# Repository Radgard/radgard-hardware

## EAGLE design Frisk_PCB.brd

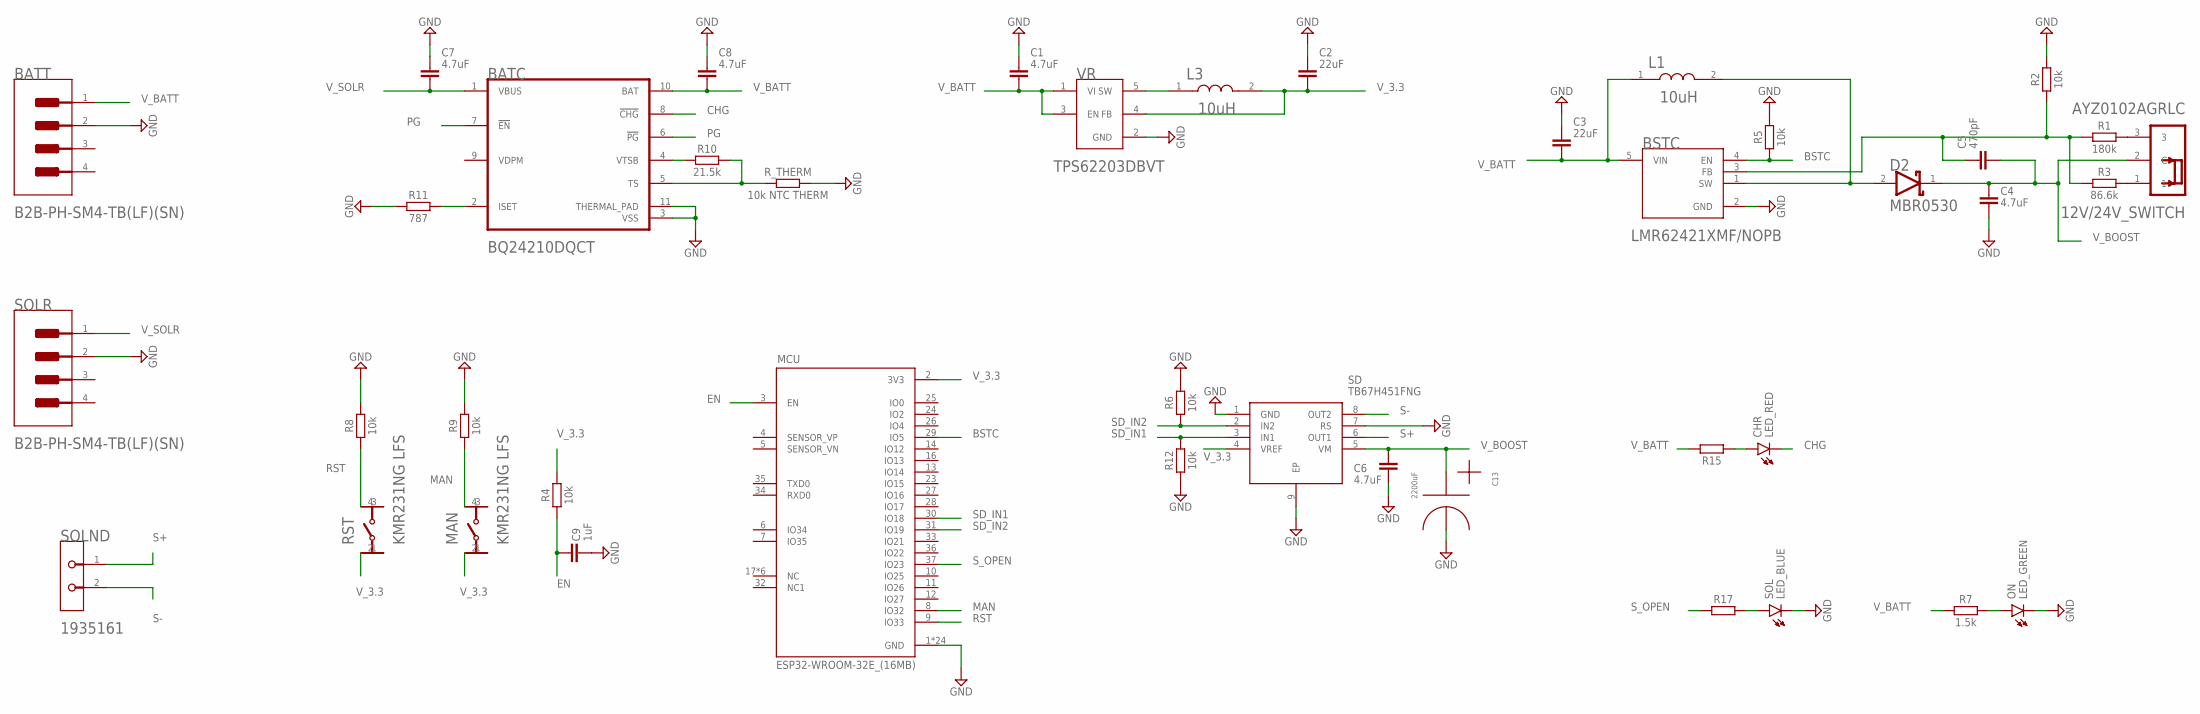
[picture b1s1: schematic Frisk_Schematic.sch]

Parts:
12V/24V_SWITCH: C&K_AYZ0102AGRLCC&K_AYZ0102AGRLC_0_0; C&K_AYZ0102AGRLC_0
BATC: TEXAS_INSTRUMENTS_BQ24210DQCTTEXAS_INSTRUMENTS_BQ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; TEXAS_INSTRUMENTS_BQ24210DQCT_2
BATT: JST_B2B-PH-SM4-TB_LF_SNJST_B2B-PH-SM4-TB_LF_SN_0_0; JST_B2B-PH-SM4-TB_LF_SN_0
BSTC: TEXAS_INSTRUMENTS_LMR62421XMF-NOPBTEXAS_INSTRUMEN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; TEXAS_INSTRUMENTS_LMR62421XMF-NOPB_0
C1, C4, C6, C7, C8: 4.7uF; CAPC1608X85
C2, C3: 22uF; CAPC3225X135
C5: 470pF; CAPC1608X85
C9: 1uF; CAPC1608X85
C13: UVZ1E222; CAPPRD500W60D1250H2700
CHR: LED_RED; LEDC1608X65N_RND-R
D2: ON_SEMI_MBR0530ON_SEMI_MBR0530_0_2; ON_SEMI_MBR0530_2
L1, L3: VISHAY_IHLP2525CZER100M01VISHAY_IHLP2525CZER100M0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; VISHAY_IHLP2525CZER100M01_0
MAN: C&K_COMPONENTS_KMR231NG_LFSC&K_COMPONENTS_KMR231N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; C&K_COMPONENTS_KMR231NG_LFS_0
MCU: ESP32-WROOM-32E_(16MB); MODULE_ESP32-WROOM-32E_(16MB)
ON: LED_GREEN; LEDC1608X65N_RND-R
R1: 180k; RESC1608X60
R2, R4, R5, R6, R8, R9, R12: 10k; RESC1608X60
R3: 86.6k; RESC1608X60
R7, R15, R17: 1.5k; RESC1608X60
R10: 21.5k; RESC1608X60
R11: 787; RESC1608X60
RST: C&K_COMPONENTS_KMR231NG_LFSC&K_COMPONENTS_KMR231N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; C&K_COMPONENTS_KMR231NG_LFS_0
R_THERM: 10k NTC THERM; RESC1608X60
SD: TB67H451FNG; SOIC127P600X170-9N
SOL: LED_BLUE; LEDC1608X65N_RND-R
SOLND: PHOENIX_CONTACT_1935161PHOENIX_CONTACT_1935161_0_0; PHOENIX_CONTACT_1935161_0
SOLR: JST_B2B-PH-SM4-TB_LF_SNJST_B2B-PH-SM4-TB_LF_SN_0_0; JST_B2B-PH-SM4-TB_LF_SN_0
VR: TEXAS_INSTRUMENTS_TPS62203DBVTTEXAS_INSTRUMENTS_T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; TEXAS_INSTRUMENTS_TPS62203DBVT_0

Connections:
BSTC: BSTC.4 (EN), MCU.29 (IO5), R5.1
CHG: BATC.8 (!CHG!), CHR.C
EN: C9.1, MCU.3 (EN), R4.1
GND: BATC.3 (VSS), BATC.11 (THERMAL_PAD), BATT.2, BSTC.2 (GND), C1.1, C2.1, C3.1, C4.2, C6.2, C7.1, C8.1, C9.2, C13.N (2), MCU.1 (GND), MCU.15 (GND), MCU.38 (GND), MCU.39_1 (GND), MCU.39_2 (GND), MCU.39_3 (GND), MCU.39_4 (GND), MCU.39_5 (GND), MCU.39_6 (GND), MCU.39_7 (GND), MCU.39_8 (GND), MCU.39_9 (GND), MCU.39_10 (GND), MCU.39_11 (GND), MCU.39_12 (GND), MCU.39_13 (GND), MCU.39_14 (GND), MCU.39_15 (GND), MCU.39_16 (GND), MCU.39_17 (GND), MCU.39_18 (GND), MCU.39_19 (GND), MCU.39_20 (GND), MCU.39_21 (GND), ON.C, R2.2, R5.2, R6.2, R8.2, R9.2, R11.1, R12.1, R_THERM.2, SD.1 (GND), SD.7 (RS), SD.9 (EP), SOL.C, SOLR.2, VR.2 (GND)
MAN: MAN.4, MCU.8 (IO32), R9.1
unnamed: CHR.A, R15.1
unnamed: L3.1, VR.5 (SW)
unnamed: ON.A, R7.2
unnamed: BATC.5 (TS), R10.2, R_THERM.1
unnamed: BSTC.1 (SW), D2.2 (ANODE), L1.2
unnamed: BSTC.3 (FB), C5.1, R1.1, R2.1, R3.1
unnamed: 12V/24V_SWITCH.3, R1.2
unnamed: 12V/24V_SWITCH.1, R3.2
unnamed: BATC.4 (VTSB), R10.1
unnamed: BATC.2 (ISET), R11.2
unnamed: R17.2, SOL.A
PG: BATC.6 (!PG!), BATC.7 (!EN!)
RST: MCU.9 (IO33), R8.1, RST.4
S+: SD.6 (OUT1), SOLND.1
S-: SD.8 (OUT2), SOLND.2
SD_IN1: MCU.30 (IO18), R12.2, SD.3 (IN1)
SD_IN2: MCU.31 (IO19), R6.1, SD.2 (IN2)
S_OPEN: MCU.37 (IO23), R17.1
VDPM: BATC.9 (VDPM)
V_3.3: C2.2, L3.2, MAN.2, MCU.2 (3V3), R4.2, RST.2, SD.4 (VREF), VR.4 (FB)
V_BATT: BATC.10 (BAT), BATT.1, BSTC.5 (VIN), C1.2, C3.2, C8.2, L1.1, R7.1, R15.2, VR.1 (VI), VR.3 (EN)
V_BOOST: 12V/24V_SWITCH.2 (C), C4.1, C5.2, C6.1, C13.P (1), D2.1 (CATHODE), SD.5 (VM)
V_SOLR: BATC.1 (VBUS), C7.2, SOLR.1

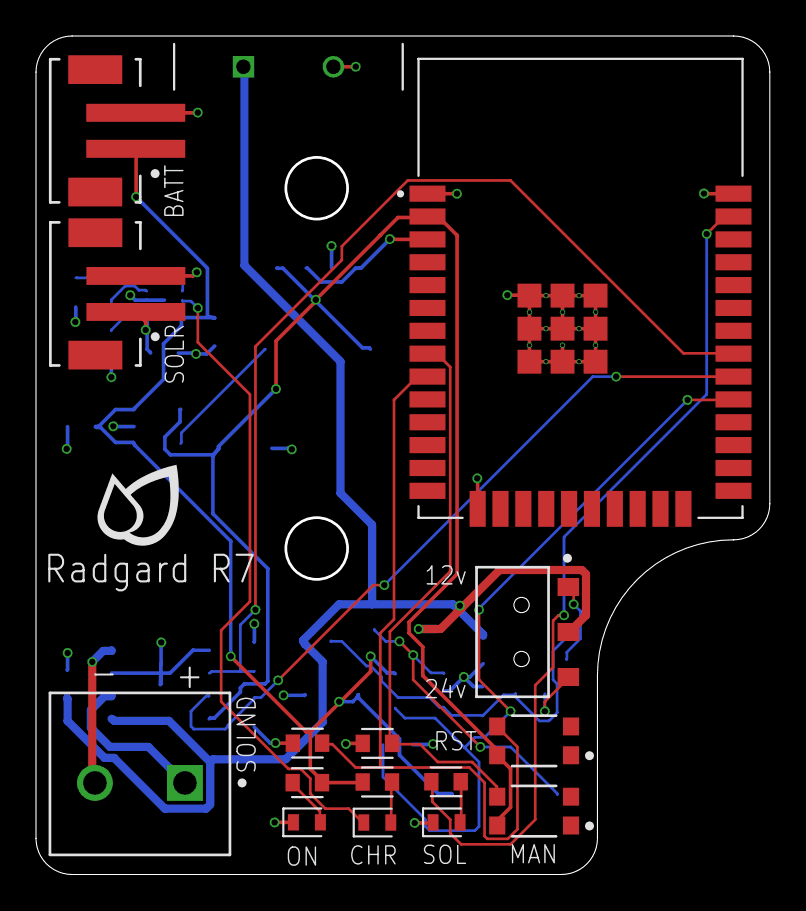
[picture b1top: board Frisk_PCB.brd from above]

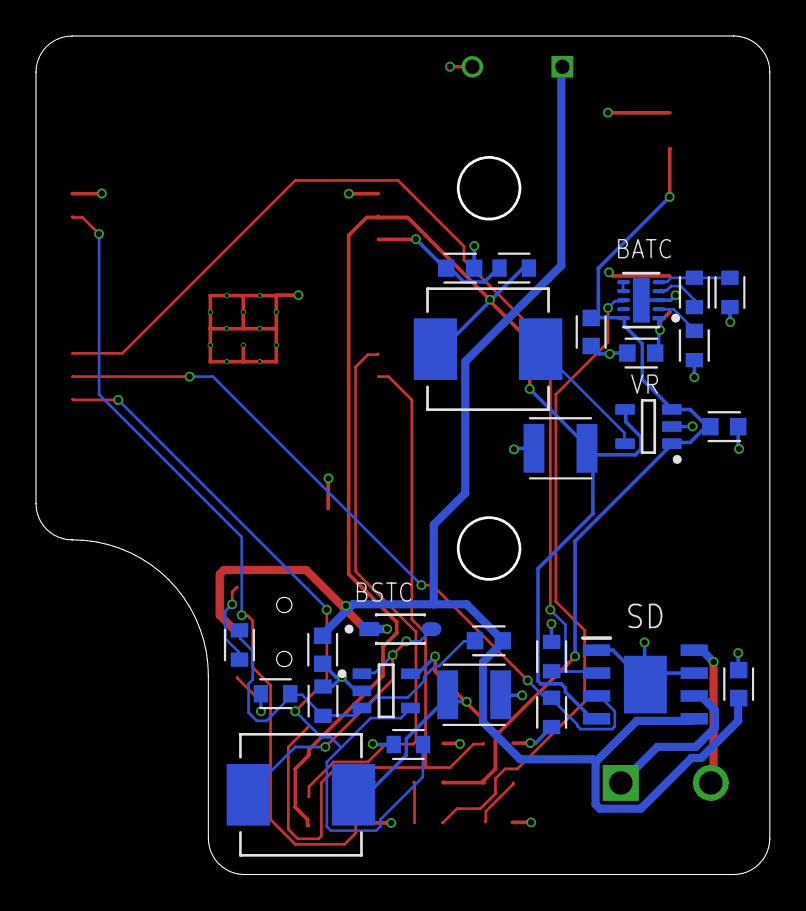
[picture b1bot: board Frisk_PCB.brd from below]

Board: 4 copper layers, 40.6 x 46.4 mm, 42 parts (26 on the bottom side), 27 nets.
